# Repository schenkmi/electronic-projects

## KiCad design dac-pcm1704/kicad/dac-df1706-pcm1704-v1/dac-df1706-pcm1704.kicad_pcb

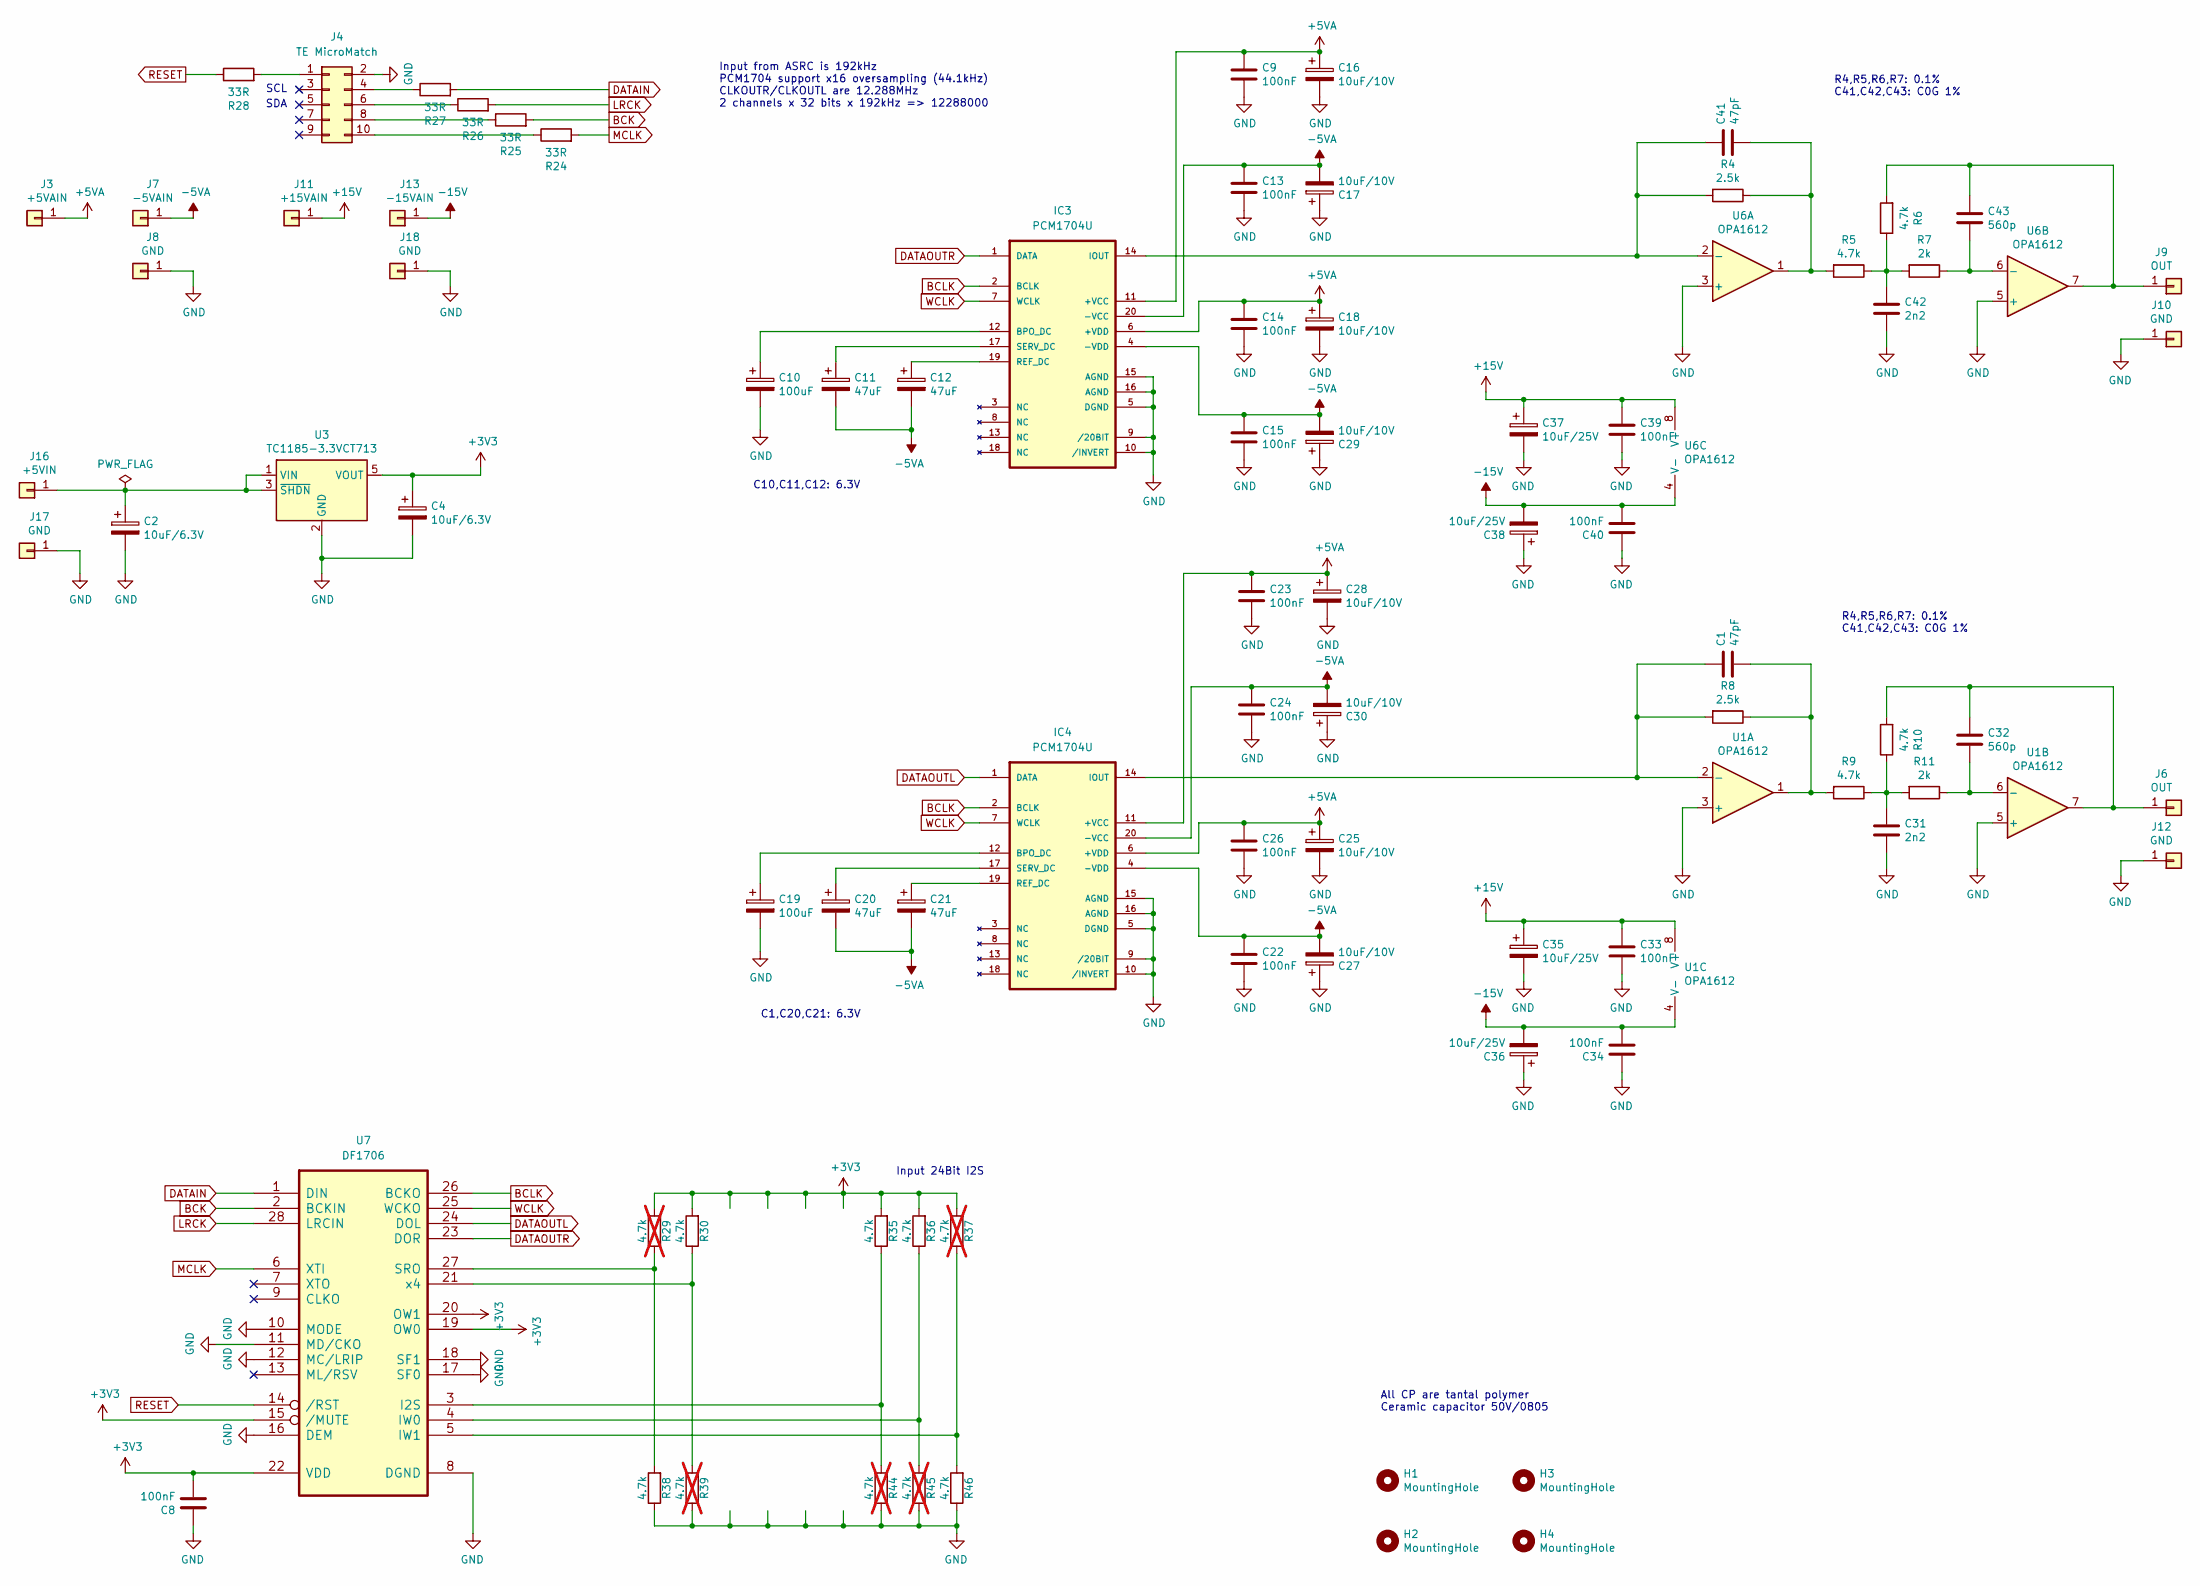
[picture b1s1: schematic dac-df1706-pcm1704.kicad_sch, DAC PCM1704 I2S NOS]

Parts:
C1, C41: 47pF; C_0805_2012Metric_Pad1.18x1.45mm_HandSolder
C2, C4: 10uF/6.3V; C_0805_2012Metric_Pad1.18x1.45mm_HandSolder
C8, C9, C13, C14, C15, C22, C23, C24, C26, C33, C34, C39, C40: 100nF; C_0805_2012Metric_Pad1.18x1.45mm_HandSolder
C10, C19: 100uF; C_1206_3216Metric_Pad1.33x1.80mm_HandSolder
C11, C12, C20, C21: 47uF; C_1206_3216Metric_Pad1.33x1.80mm_HandSolder
C16, C17, C18, C25, C27, C28, C29, C30: 10uF/10V; C_1206_3216Metric_Pad1.33x1.80mm_HandSolder
C31, C42: 2n2; C_0805_2012Metric_Pad1.18x1.45mm_HandSolder
C32, C43: 560p; C_0805_2012Metric_Pad1.18x1.45mm_HandSolder
C35, C36, C37, C38: 10uF/25V; C_1206_3216Metric_Pad1.33x1.80mm_HandSolder
H1, H2, H3, H4: MountingHole; MountingHole_3.2mm_M3
IC3, IC4: PCM1704U; SO-20_5.3x12.6mm_P1.27mm; MPN PCM1702P-J
J3: +5VAIN; Pin_D1.0mm_L10.0mm
J4: TE MicroMatch; TE_Micro-MaTch_1-215079-0_2x05_P1.27mm_Vertical
J6, J9: OUT; Pin_D1.0mm_L10.0mm
J7: -5VAIN; Pin_D1.0mm_L10.0mm
J8, J10, J12, J17, J18: GND; Pin_D1.0mm_L10.0mm
J11: +15VAIN; Pin_D1.0mm_L10.0mm
J13: -15VAIN; Pin_D1.0mm_L10.0mm
J16: +5VIN; Pin_D1.0mm_L10.0mm
R4, R8: 2.5k; R_0805_2012Metric_Pad1.20x1.40mm_HandSolder
R5, R6, R9, R10: 4.7k; R_0805_2012Metric_Pad1.20x1.40mm_HandSolder
R7, R11: 2k; R_0805_2012Metric_Pad1.20x1.40mm_HandSolder
R24, R25, R26, R27, R28: 33R; R_0603_1608Metric_Pad0.98x0.95mm_HandSolder
R29, R37, R39, R44, R45: 4.7k; R_0603_1608Metric_Pad0.98x0.95mm_HandSolder; not fitted
R30, R35, R36, R38, R46: 4.7k; R_0603_1608Metric_Pad0.98x0.95mm_HandSolder
U1, U6: OPA1612; SOIC-8_3.9x4.9mm_P1.27mm
U3: TC1185-3.3VCT713; SOT-23-5
U7: DF1706; SSOP-28_5.3x10.2mm_P0.65mm

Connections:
+3V3: C4.1, C8.2, R29.2, R30.2, R35.2, R36.2, R37.2, U3.5 (VOUT), U7.15 (/MUTE), U7.19 (OW0), U7.20 (OW1), U7.22 (VDD)
+5VA: C9.1, C14.1, C16.1, C18.1, C23.1, C25.1, C26.1, C28.1, IC3.6 (+VDD), IC3.11 (+VCC), IC4.6 (+VDD), IC4.11 (+VCC), J3.1
+15V: C33.1, C35.1, C37.1, C39.1, J11.1, U1.8 (V+), U6.8 (V+)
-5VA: C11.2, C12.2, C13.1, C15.1, C17.2, C20.2, C21.2, C22.1, C24.1, C27.2, C29.2, C30.2, IC3.4 (-VDD), IC3.20 (-VCC), IC4.4 (-VDD), IC4.20 (-VCC), J7.1
-15V: C34.2, C36.2, C38.2, C40.2, J13.1, U1.4 (V-), U6.4 (V-)
BCK: R25.2, U7.2 (BCKIN)
BCLK: IC3.2 (BCLK), IC4.2 (BCLK), U7.26 (BCKO)
DATAIN: R27.2, U7.1 (DIN)
DATAOUTL: IC4.1 (DATA), U7.24 (DOL)
DATAOUTR: IC3.1 (DATA), U7.23 (DOR)
GND: C2.2, C4.2, C8.1, C9.2, C10.2, C13.2, C14.2, C15.2, C16.2, C17.1, C18.2, C19.2, C22.2, C23.2, C24.2, C25.2, C26.2, C27.1, C28.2, C29.1, C30.1, C31.2, C33.2, C34.1, C35.2, C36.1, C37.2, C38.1, C39.2, C40.1, C42.2, IC3.5 (DGND), IC3.9 (/20BIT), IC3.10 (/INVERT), IC3.15 (AGND), IC3.16 (AGND), IC4.5 (DGND), IC4.9 (/20BIT), IC4.10 (/INVERT), IC4.15 (AGND), IC4.16 (AGND), J4.2, J8.1, J10.1, J12.1, J17.1, J18.1, R38.1, R39.1, R44.1, R45.1, R46.1, U1.3 (+), U1.5 (+), U3.2 (GND), U6.3 (+), U6.5 (+), U7.8 (DGND), U7.10 (MODE), U7.11 (MD/CKO), U7.12 (MC/LRIP), U7.16 (DEM), U7.17 (SF0), U7.18 (SF1)
LRCK: R26.2, U7.28 (LRCIN)
MCLK: R24.2, U7.6 (XTI)
unnamed: C1.2, R8.1, R9.2, U1.1
unnamed: C31.1, R9.1, R10.1, R11.2
unnamed: C41.2, R4.1, R5.2, U6.1
unnamed: C42.1, R5.1, R6.1, R7.2
unnamed: C10.1, IC3.12 (BPO_DC)
unnamed: C41.1, IC3.14 (IOUT), R4.2, U6.2 (-)
unnamed: C12.1, IC3.19 (REF_DC)
unnamed: C11.1, IC3.17 (SERV_DC)
unnamed: C19.1, IC4.12 (BPO_DC)
unnamed: C1.1, IC4.14 (IOUT), R8.2, U1.2 (-)
unnamed: C21.1, IC4.19 (REF_DC)
unnamed: C20.1, IC4.17 (SERV_DC)
unnamed: J4.1, R28.2
unnamed: J4.4, R27.1
unnamed: J4.6, R26.1
unnamed: J4.8, R25.1
unnamed: J4.10, R24.1
unnamed: C32.1, J6.1, R10.2, U1.7
unnamed: C43.1, J9.1, R6.2, U6.7
unnamed: C2.1, J16.1, U3.1 (VIN), U3.3 (~SHDN)
unnamed: C32.2, R11.1, U1.6 (-)
unnamed: C43.2, R7.1, U6.6 (-)
unnamed: R35.1, R44.2, U7.3 (I2S)
unnamed: R36.1, R45.2, U7.4 (IW0)
unnamed: R37.1, R46.2, U7.5 (IW1)
unnamed: R29.1, R38.2, U7.27 (SRO)
unnamed: R30.1, R39.2, U7.21 (x4)
RESET: R28.1, U7.14 (/RST)
WCLK: IC3.7 (WCLK), IC4.7 (WCLK), U7.25 (WCKO)

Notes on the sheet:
All CP are tantal polymer Ceramic capacitor 50V/0805
R4,R5,R6,R7: 0.1% C41,C42,C43: C0G 1%
Input 24Bit I2S
C1,C20,C21: 6.3V
C10,C11,C12: 6.3V
Input from ASRC is 192kHz PCM1704 support x16 oversampling (44.1kHz) CLKOUTR/CLKOUTL are 12.288MHz 2 channels x 32 bits x 192kHz => 12288000
SCL
SDA

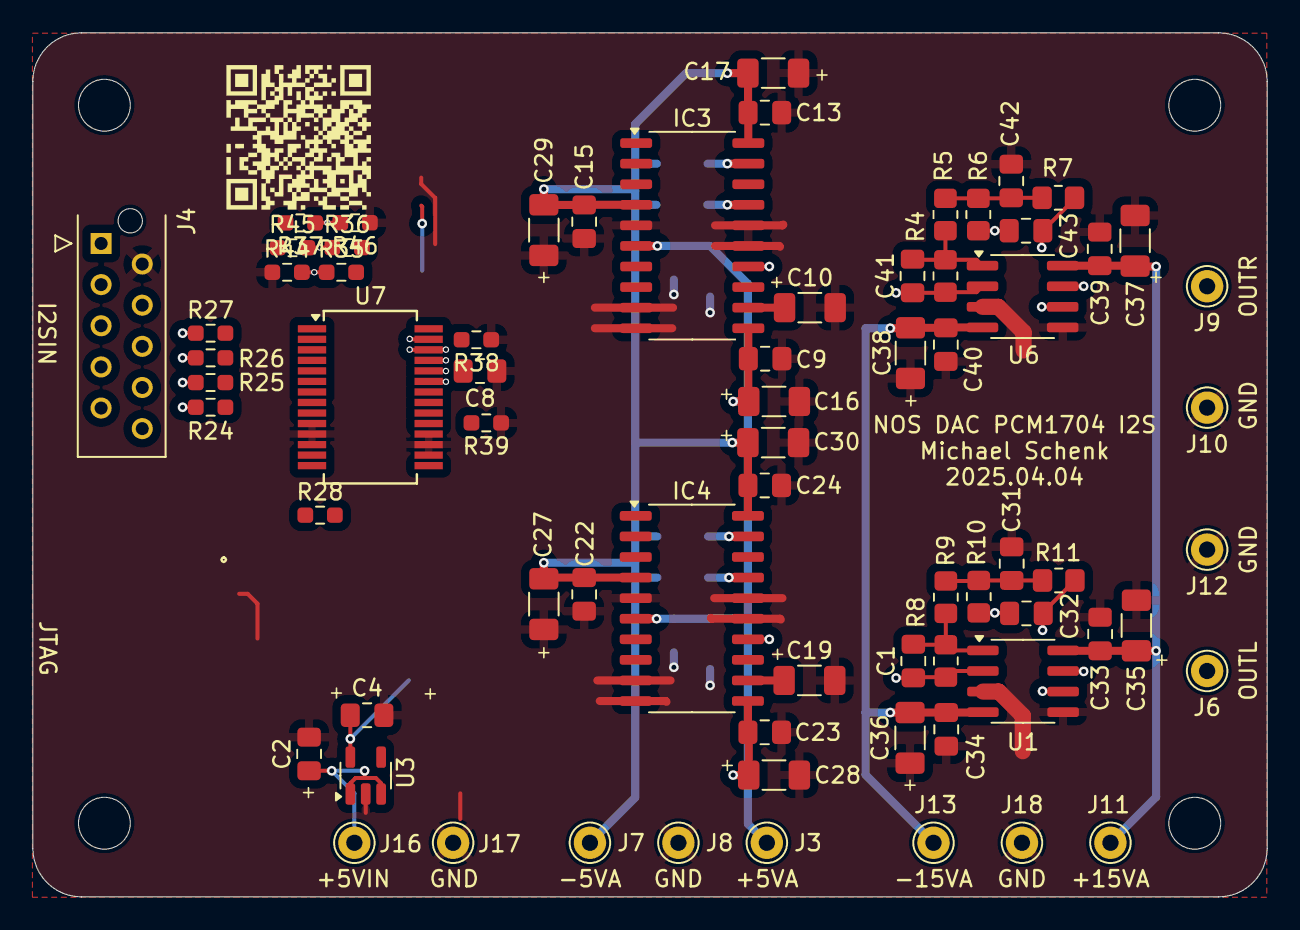
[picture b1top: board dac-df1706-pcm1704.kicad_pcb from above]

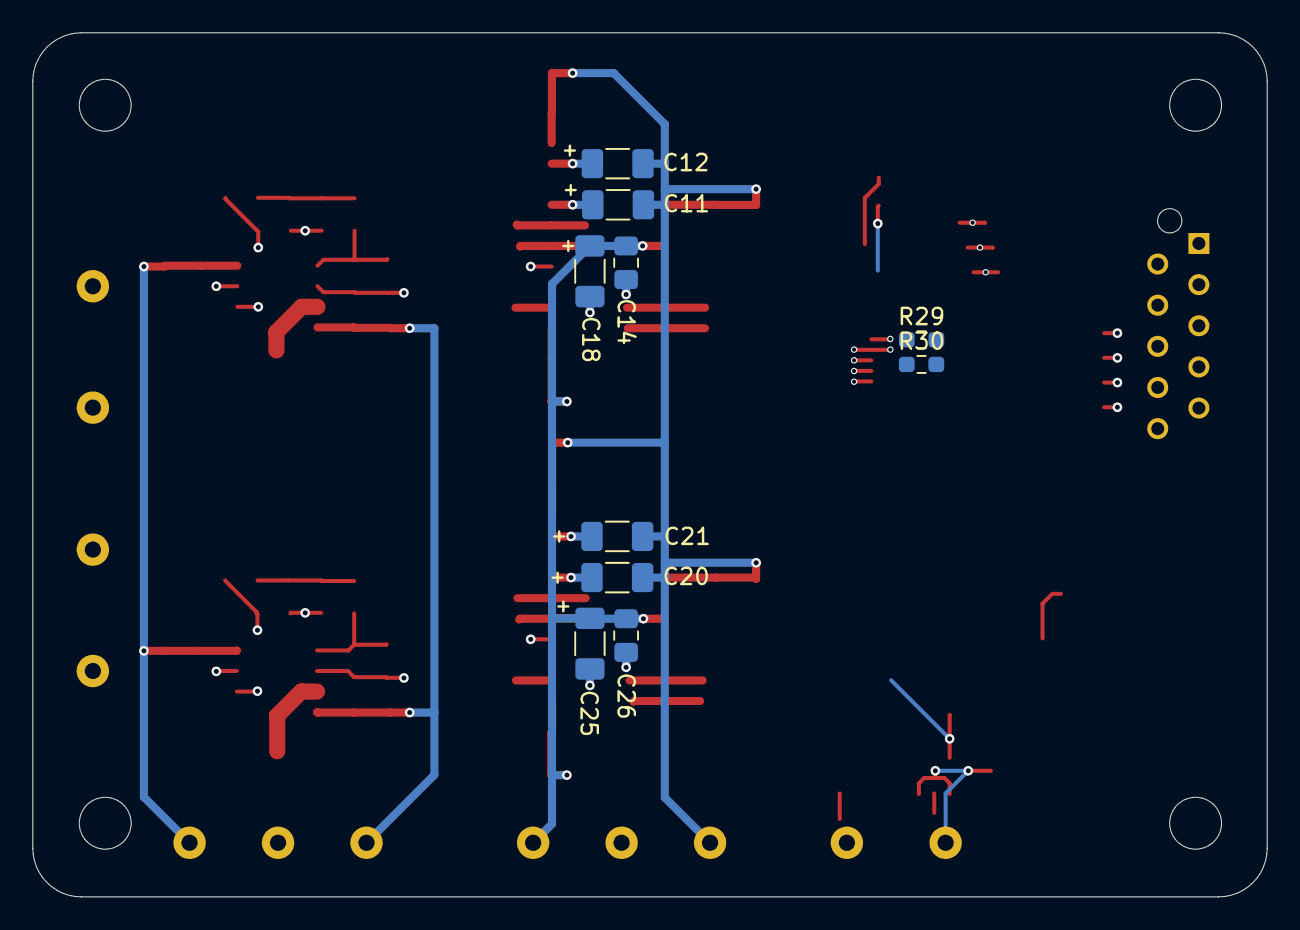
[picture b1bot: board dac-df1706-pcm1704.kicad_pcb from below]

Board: 4 copper layers, 76.2 x 53.3 mm, 85 parts (10 on the bottom side), 42 nets.

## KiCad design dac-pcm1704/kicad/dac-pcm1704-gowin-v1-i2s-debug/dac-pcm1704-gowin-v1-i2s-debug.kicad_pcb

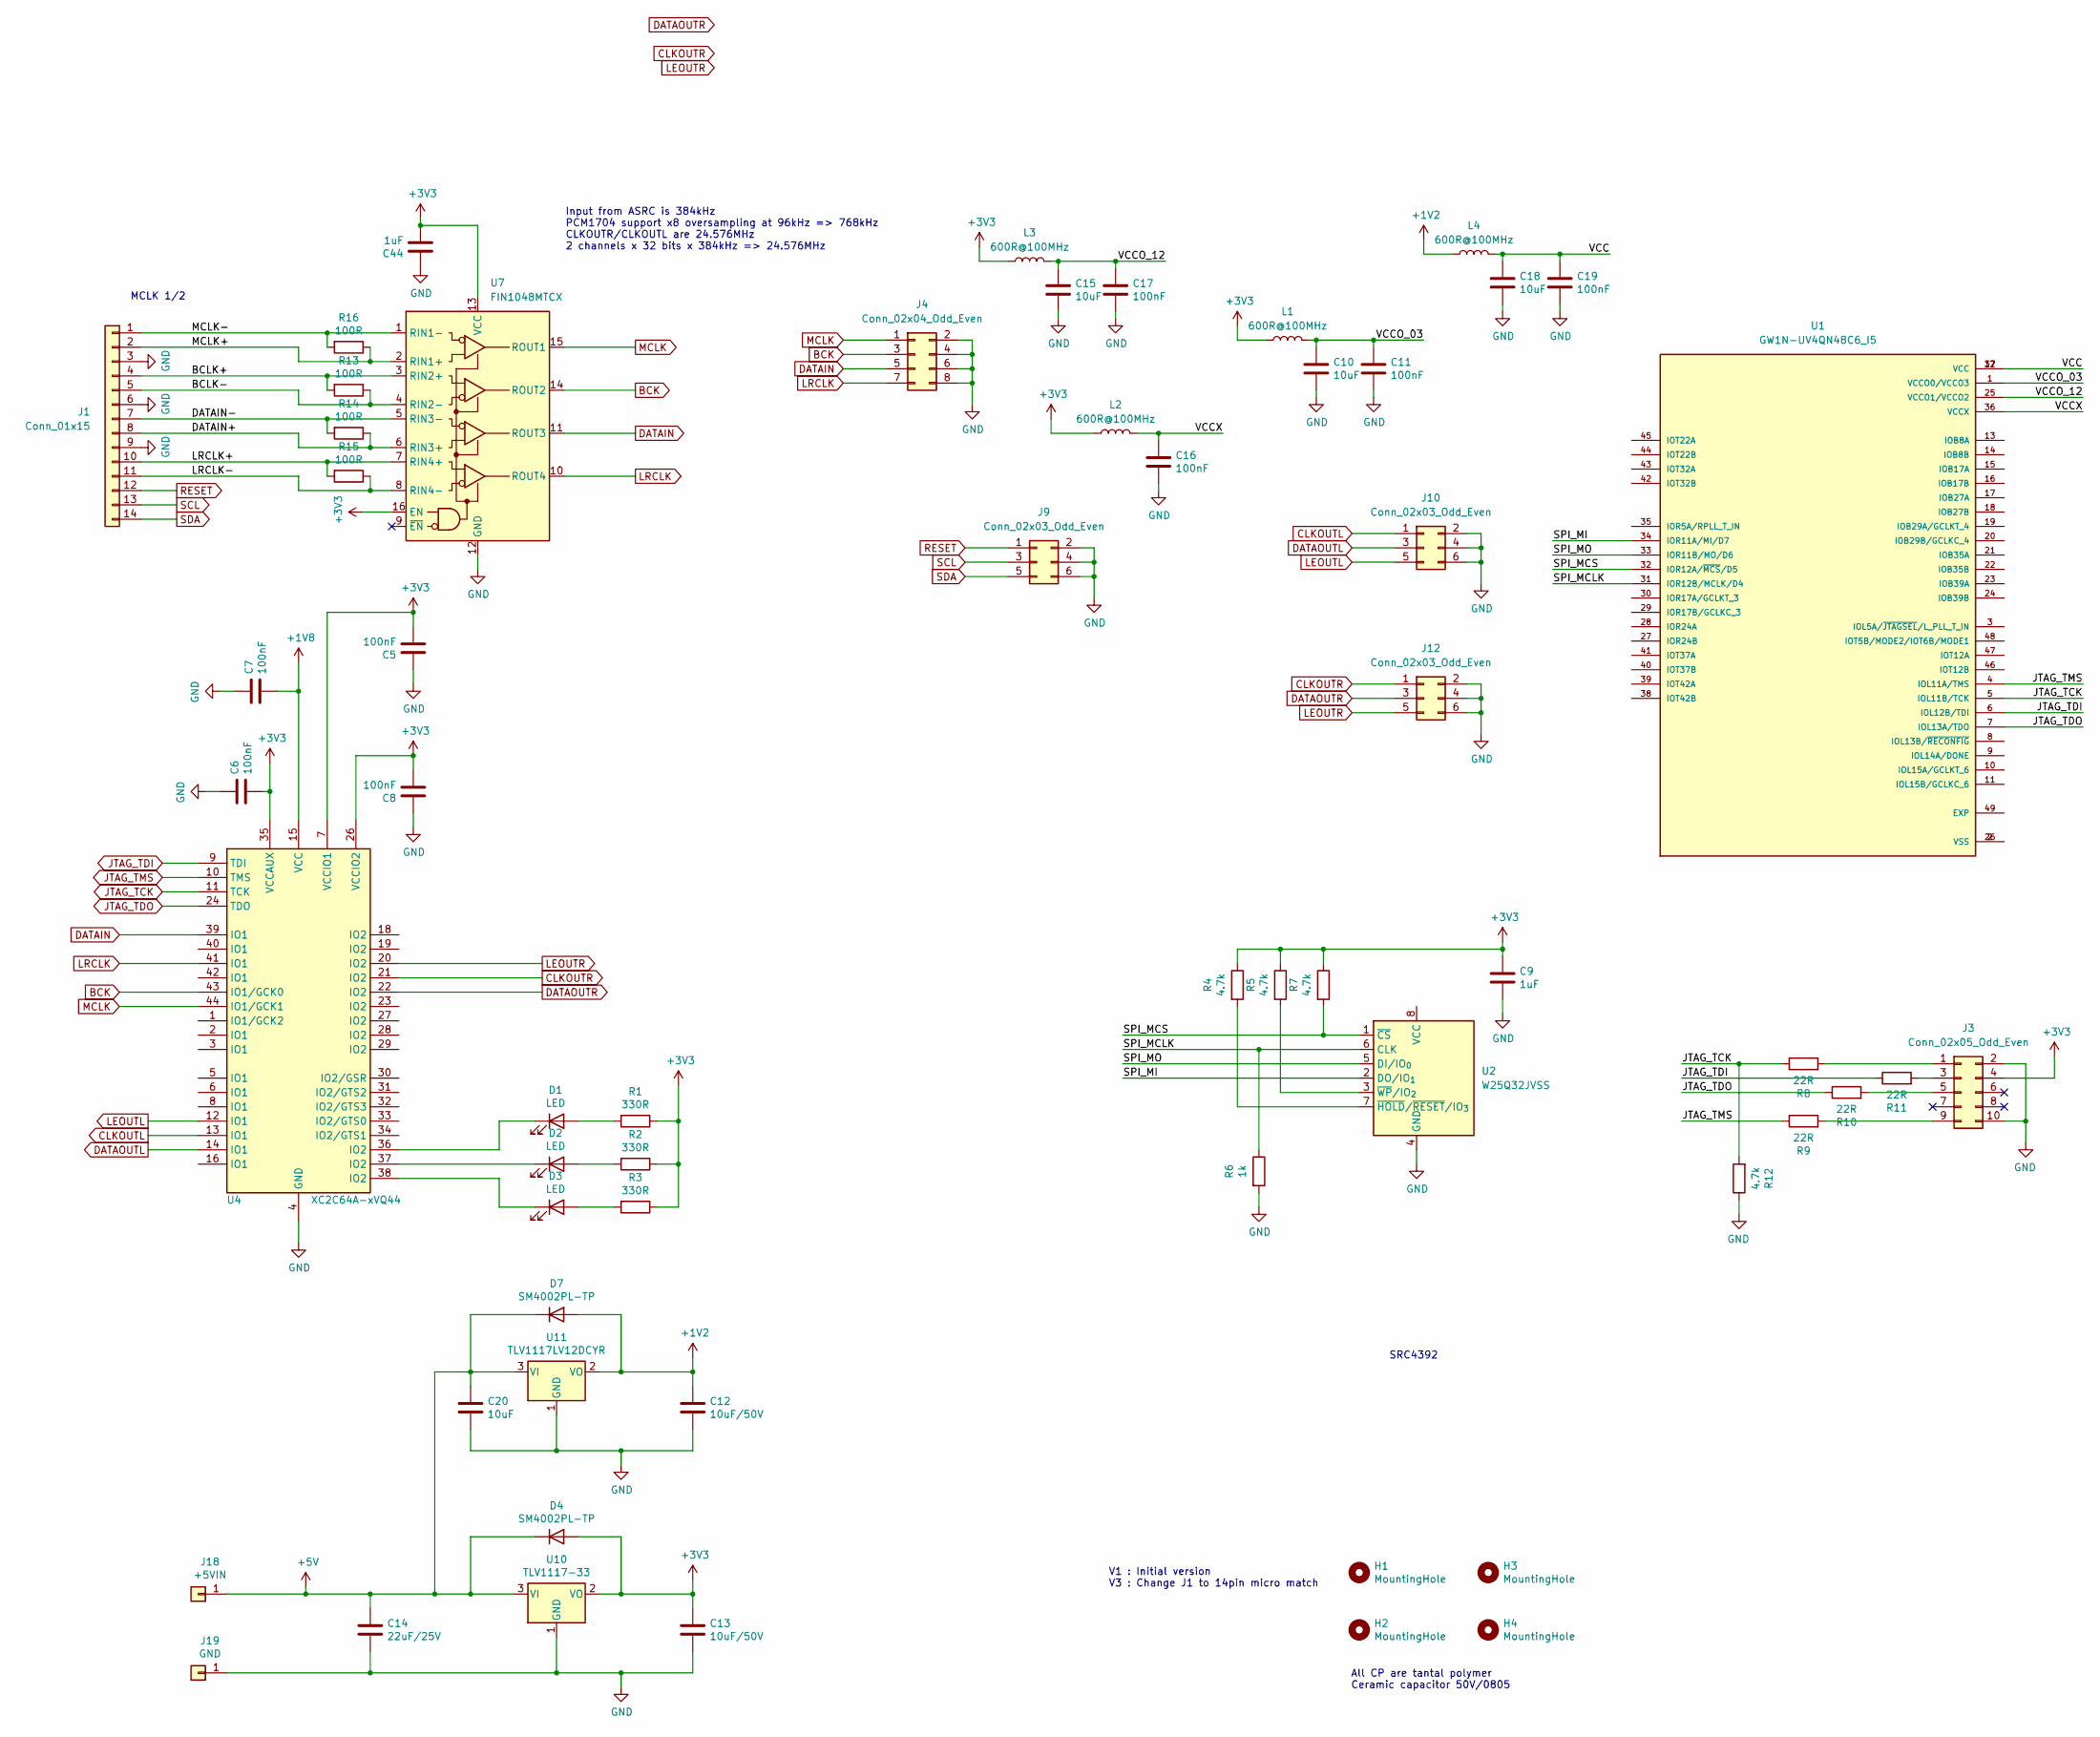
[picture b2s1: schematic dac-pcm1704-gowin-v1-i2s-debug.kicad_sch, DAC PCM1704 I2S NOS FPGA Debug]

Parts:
C5, C6, C7, C8, C11, C16, C17, C19: 100nF; C_0603_1608Metric_Pad1.08x0.95mm_HandSolder
C9, C44: 1uF; C_0603_1608Metric_Pad1.08x0.95mm_HandSolder
C10, C15, C18: 10uF; C_0603_1608Metric_Pad1.08x0.95mm_HandSolder
C12, C13: 10uF/50V; C_1206_3216Metric_Pad1.33x1.80mm_HandSolder
C14: 22uF/25V; C_1210_3225Metric_Pad1.33x2.70mm_HandSolder
C20: 10uF; C_1206_3216Metric_Pad1.33x1.80mm_HandSolder
D1, D2, D3: LED; LED_0805_2012Metric_Pad1.15x1.40mm_HandSolder
D4, D7: SM4002PL-TP; D_SOD-123F
H1, H2, H3, H4: MountingHole; MountingHole_3.2mm_M3
J1: Conn_01x15; TE_Micro-MaTch_1-215079-4_2x07_P1.27mm_Vertical
J3: Conn_02x05_Odd_Even; PinHeader_2x05_P2.54mm_Vertical
J4: Conn_02x04_Odd_Even; PinHeader_2x04_P2.54mm_Vertical
J9, J10, J12: Conn_02x03_Odd_Even; PinHeader_2x03_P2.54mm_Vertical
J18: +5VIN; Pin_D1.0mm_L10.0mm
J19: GND; Pin_D1.0mm_L10.0mm
L1, L2, L3, L4: 600R@100MHz; L_0603_1608Metric_Pad1.05x0.95mm_HandSolder
R1, R2, R3: 330R; R_0603_1608Metric_Pad0.98x0.95mm_HandSolder
R4, R5, R7, R12: 4.7k; R_0603_1608Metric_Pad0.98x0.95mm_HandSolder
R6: 1k; R_0603_1608Metric_Pad0.98x0.95mm_HandSolder
R8, R9, R10, R11: 22R; R_0603_1608Metric_Pad0.98x0.95mm_HandSolder
R13, R14, R15, R16: 100R; R_0402_1005Metric_Pad0.72x0.64mm_HandSolder
U1: GW1N-UV4QN48C6_I5; QFN-48-1EP_6x6mm_P0.4mm_EP4.2x4.2mm; PARTREV 2.2E
U2: W25Q32JVSS; SOIC-8_5.3x5.3mm_P1.27mm
U4: XC2C64A-xVQ44; TQFP-44_10x10mm_P0.8mm
U7: FIN1048MTCX; TSSOP-16_4.4x5mm_P0.65mm; Part Number FIN1047MTCX
U10: TLV1117-33; SOT-223-3_TabPin2
U11: TLV1117LV12DCYR; SOT-223-3_TabPin2

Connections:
+1V2: C12.1, D7.2 (A), L4.1, U11.2 (VO)
+1V8: C7.2, U4.15 (VCC)
+3V3: C5.2, C6.2, C8.2, C9.1, C13.1, C44.2, D4.2 (A), J3.4, L1.1, L2.1, L3.1, R1.1, R2.1, R3.1, R4.1, R5.1, R7.1, U4.7 (VCCIO1), U4.26 (VCCIO2), U4.35 (VCCAUX), U7.13 (VCC), U7.16 (EN), U10.2 (VO)
+5V: C14.1, C20.1, D4.1 (K), D7.1 (K), J18.1, U10.3 (VI), U11.3 (VI)
/BCLK+: J1.4, R13.2, U7.3 (RIN2+)
/BCLK-: J1.5, R13.1, U7.4 (RIN2-)
/DATAIN+: J1.8, R14.1, U7.6 (RIN3+)
/DATAIN-: J1.7, R14.2, U7.5 (RIN3-)
/LRCLK+: J1.10, R15.2, U7.7 (RIN4+)
/LRCLK-: J1.11, R15.1, U7.8 (RIN4-)
/MCLK+: J1.2, R16.1, U7.2 (RIN1+)
/MCLK-: J1.1, R16.2, U7.1 (RIN1-)
/SPI_MCLK: R6.1, U1.31 (IOR12B/MCLK/D4), U2.6 (CLK)
/SPI_MCS: R7.2, U1.32 (IOR12A/~MCS/D5), U2.1 (~CS)
/SPI_MI: U1.34 (IOR11A/MI/D7), U2.2 (DO/IO_{1})
/SPI_MO: U1.33 (IOR11B/MO/D6), U2.5 (DI/IO_{0})
/VCC: C18.1, C19.1, L4.2, U1.12 (VCC), U1.37 (VCC)
/VCCO_03: C10.1, C11.1, L1.2, U1.1 (VCCO0/VCCO3)
/VCCO_12: C15.1, C17.1, L3.2, U1.25 (VCCO1/VCCO2)
/VCCX: C16.1, L2.2, U1.36 (VCCX)
BCK: J4.3, U4.43 (IO1/GCK0), U7.14 (ROUT2)
CLKOUTL: J10.1, U4.13 (IO1)
CLKOUTR: J12.1, U4.21 (IO2)
DATAIN: J4.5, U4.39 (IO1), U7.11 (ROUT3)
DATAOUTL: J10.3, U4.14 (IO1)
DATAOUTR: J12.3, U4.22 (IO2)
GND: C5.1, C6.1, C7.1, C8.1, C9.2, C10.2, C11.2, C12.2, C13.2, C14.2, C15.2, C16.2, C17.2, C18.2, C19.2, C20.2, C44.1, J1.3, J1.6, J1.9, J3.2, J3.10, J4.2, J4.4, J4.6, J4.8, J9.2, J9.4, J9.6, J10.2, J10.4, J10.6, J12.2, J12.4, J12.6, J19.1, R6.2, R12.1, U2.4 (GND), U4.4 (GND), U4.17 (GND), U4.25 (GND), U7.12 (GND), U10.1 (GND), U11.1 (GND)
JTAG_TCK: R8.1, R12.2, U1.5 (IOL11B/TCK), U4.11 (TCK)
JTAG_TDI: R11.1, U1.6 (IOL12B/TDI), U4.9 (TDI)
JTAG_TDO: R10.1, U1.7 (IOL13A/TDO), U4.24 (TDO)
JTAG_TMS: R9.1, U1.4 (IOL11A/TMS), U4.10 (TMS)
LEOUTL: J10.5, U4.12 (IO1)
LEOUTR: J12.5, U4.20 (IO2)
LRCLK: J4.7, U4.41 (IO1), U7.10 (ROUT4)
MCLK: J4.1, U4.44 (IO1/GCK1), U7.15 (ROUT1)
unnamed: D1.2 (A), R1.2
unnamed: D1.1 (K), U4.36 (IO2)
unnamed: D2.2 (A), R2.2
unnamed: D2.1 (K), U4.37 (IO2)
unnamed: D3.2 (A), R3.2
unnamed: D3.1 (K), U4.38 (IO2)
unnamed: J3.1, R8.2
unnamed: J3.3, R11.2
unnamed: J3.5, R10.2
unnamed: J3.9, R9.2
unnamed: U1.2 (VSS), U1.26 (VSS)
unnamed: R4.2, U2.7 (~HOLD/~RESET/IO_{3})
unnamed: R5.2, U2.3 (~WP/IO_{2})
RESET: J1.12, J9.1
SCL: J1.13, J9.3
SDA: J1.14, J9.5

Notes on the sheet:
All CP are tantal polymer Ceramic capacitor 50V/0805
V1 : Initial version V3 : Change J1 to 14pin micro match
SRC4392
Input from ASRC is 384kHz PCM1704 support x8 oversampling at 96kHz => 768kHz CLKOUTR/CLKOUTL are 24.576MHz 2 channels x 32 bits x 384kHz => 24.576MHz
MCLK 1/2

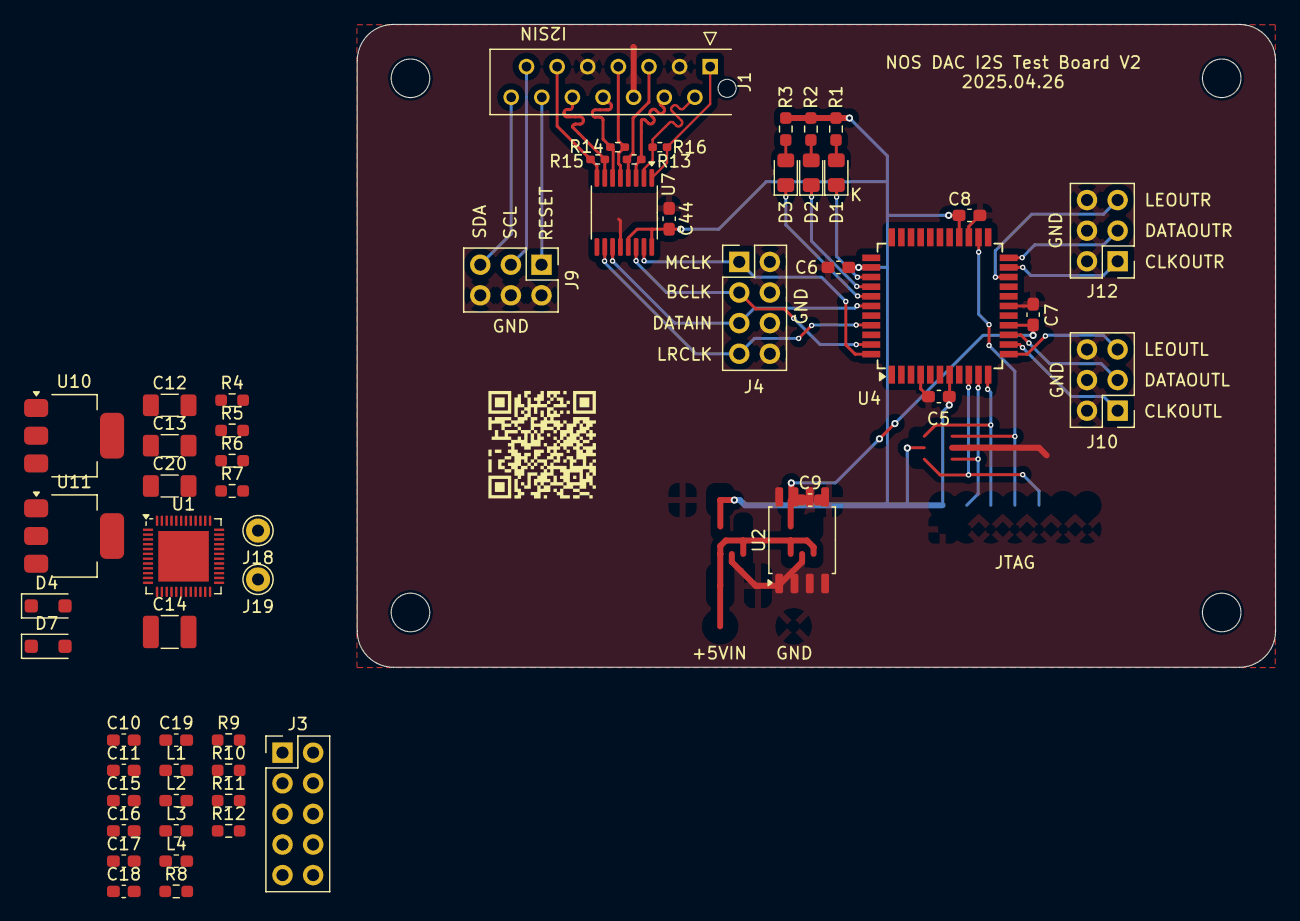
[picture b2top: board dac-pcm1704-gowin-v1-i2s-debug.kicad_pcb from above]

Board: 2 copper layers, 76.2 x 53.3 mm, 60 parts (0 on the bottom side), 51 nets.
